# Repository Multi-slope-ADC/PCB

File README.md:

# High-resolution multislope ADC - MiDi

KiCad 10 project for the MiDi build of the multislope ADC developed from Kleinstein's design and Rerouter's PCB. The schematic documents the original circuit before the 2026 modifications, as saved on 18 October 2026.

## Project and downloads

Open [the KiCad project](High%20Resolution%20Multislope%20converter-modified%20rev%202.kicad_pro) with KiCad 10 and the standard KiCad symbol, footprint and 3D model libraries. Project-specific symbols are included and use relative library paths. Exports were generated with KiCad 10.0.7.

| File | Contents |
| --- | --- |
| [Schematic PDF](docs/Schematic.pdf) | Current schematic, white background and KiCad Classic colours |
| [Schematic PNG](https://raw.githubusercontent.com/Multi-slope-ADC/PCB/refs/heads/MiDi/docs/Schematic.png) | Full-page preview |
| [Complete schematic BOM](bom/BOM-all.csv) | 231 positions, including 15 marked DNP |
| [BOM excluding DNP](bom/BOM-fitted.csv) | 216 positions, following the saved schematic flags |
| [Interactive PCB viewer](https://htmlpreview.github.io/?https://github.com/Multi-slope-ADC/PCB/blob/MiDi/bom/ibom.html) | Board footprints, values and routing; [download HTML](bom/ibom.html) to open locally |
| [PCB PDF](docs/PCB.pdf) | Colour copper and paste layer plots with silkscreen and drawing frame |
| [Gerber and drill files](gerber_to_order/) | Direct exports of the preserved PCB; [ZIP](gerber_to_order/MiDi-Gerbers.zip) |

## Schematic

## PCB views

## Assembled board

## Background and credits

- Original design discussion: [DIY high-resolution multi-slope converter](https://www.eevblog.com/forum/metrology/diy-high-resolution-multi-slope-converter/).
- Related design discussion: [Multislope design](https://www.eevblog.com/forum/projects/multislope-design/).
- PCB ancestry: [Rerouter/Multislope-ADC-PCB](https://github.com/Rerouter/Multislope-ADC-PCB).
- Interactive PCB viewer generated with [InteractiveHtmlBom](https://github.com/openscopeproject/InteractiveHtmlBom).

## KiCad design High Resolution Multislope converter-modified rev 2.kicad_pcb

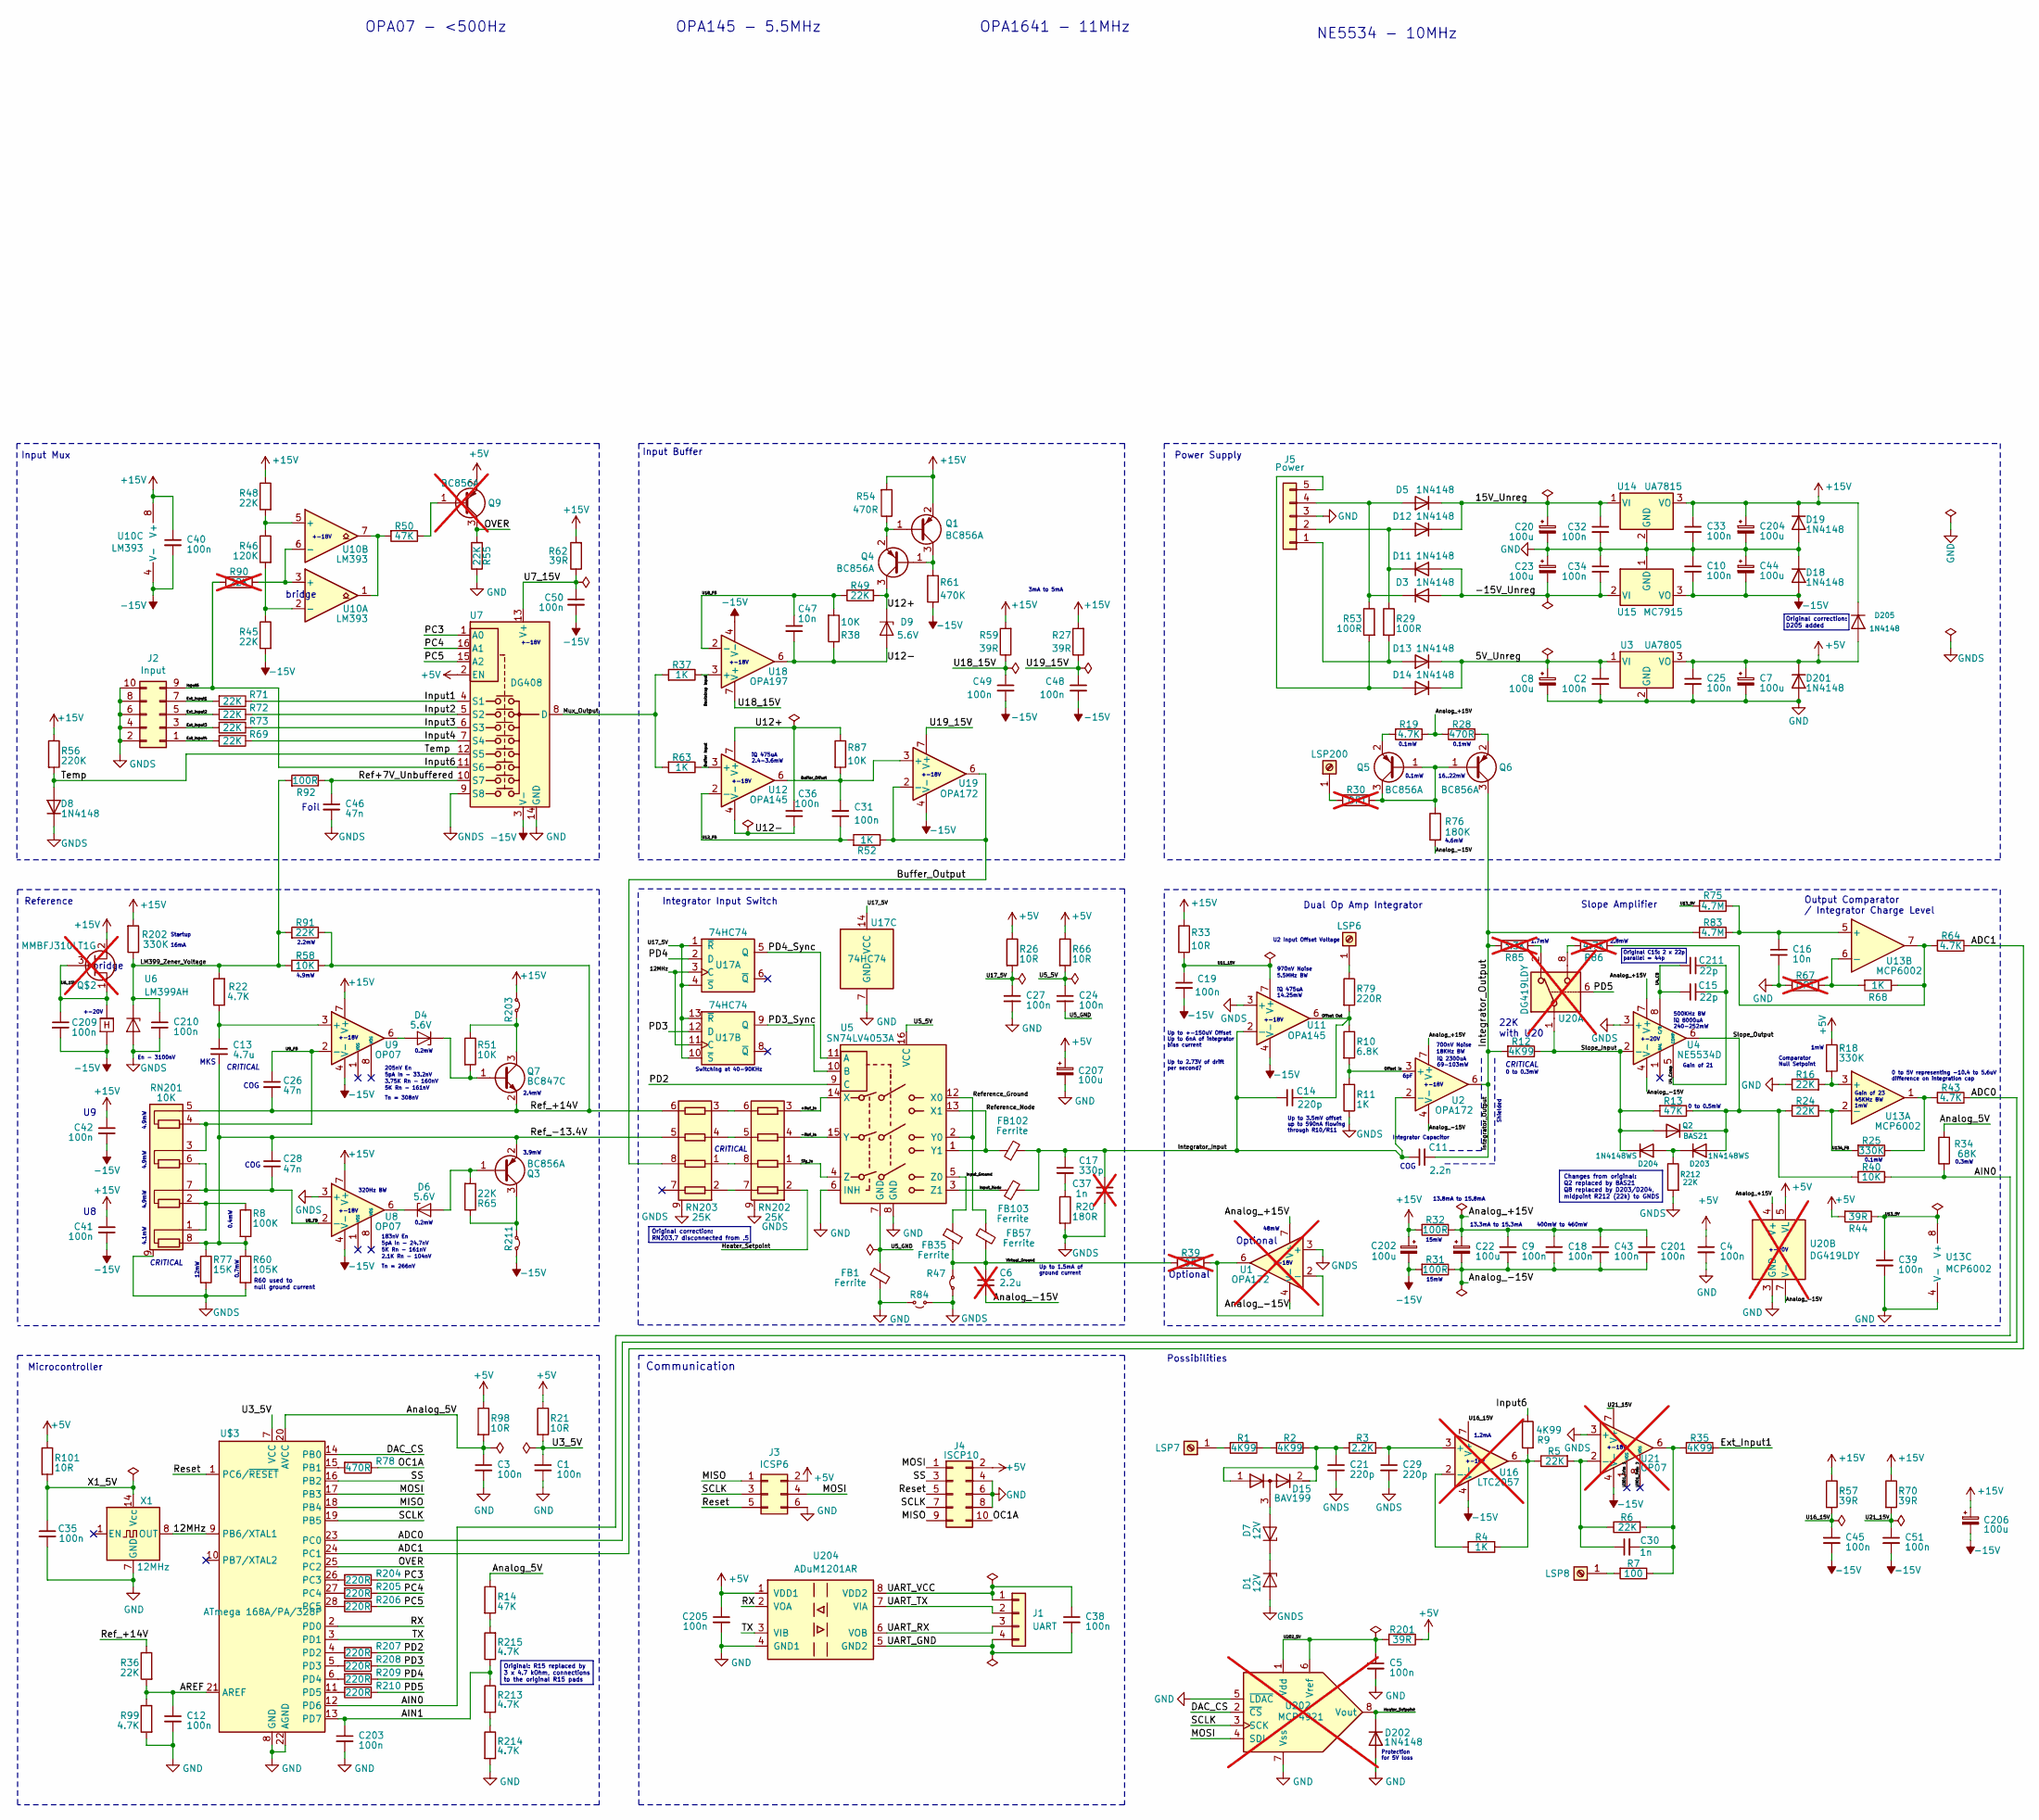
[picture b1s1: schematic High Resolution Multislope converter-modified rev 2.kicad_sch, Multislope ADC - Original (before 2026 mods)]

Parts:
C1, C2, C3, C4, C5, C9, C10, C12, C18, C19, C24, C25, C27, C32, C33, C34, C35, C36, C38, C39, C40, C41, C42, C43, C45, C48, C49, C50, C51, C201, C203, C205, C209, C210: 100n; C_0805_2012Metric; Manufacturer Part Number 08055C104KAT2A
C6: 2.2u; C_0805_2012Metric; Manufacturer Part Number CL21B225KAFNNNE; not fitted
C7, C8, C20, C22, C23, C44, C202, C204, C206, C207: 100u; CP_Radial_D8.0mm_P3.50mm; Manufacturer Part Number EEU-EB1J101
C11: 2.2n; C_0805_2012Metric; Manufacturer Part Number C2012C0G1H222J085AA
C13: 4.7u; C_Rect_L7.2mm_W7.2mm_P5.00mm_FKS2_FKP2_MKS2_MKP2; Manufacturer Part Number MKS2C044701M00KSSD
C14, C21, C29: 220p; C_0805_2012Metric; Manufacturer Part Number CL21C221JBANNNC
C15, C211: 22p; C_0805_2012Metric; Manufacturer Part Number CL21C220JBANNNC
C16, C47: 10n; C_0805_2012Metric; Manufacturer Part Number CGA4C2C0G1H103J060AA
C17: 330p; C_0805_2012Metric; Manufacturer Part Number C0805C331J5GACTU
C26, C28, C46: 47n; C_0805_2012Metric; Manufacturer Part Number C0805C473K3GECAUTO
C30: 1n; C_0805_2012Metric; Manufacturer Part Number 885012007063
C31: 100n; C_0805_2012Metric; Manufacturer Part Number C0805C473K3GECAUTO
C37: 1n; C_0805_2012Metric; Manufacturer Part Number 885012007063; not fitted
D1, D7: 12V; D_SOD-323; Manufacturer Part Number DDZ12CSF-7
D3, D5, D8, D11, D12, D13, D14, D18, D19, D201, D202: 1N4148; D_SOD-323; Manufacturer Part Number 1N4148WS
D4, D6, D9: 5.6V; D_SOD-323; Manufacturer Part Number MM3Z5V6ST1G
D15: BAV199; SOT-23; Manufacturer Part Number BAV199LT1G
D203, D204: 1N4148WS; Manufacturer Part Number 1N4148WS
D205: 1N4148; Manufacturer Part Number 1N4148
FB1, FB35, FB57, FB102, FB103: Ferrite; L_0805_2012Metric; Manufacturer Part Number MMZ2012Y152BT000
J1: UART; PinHeader_1x04_P2.54mm_Vertical
J2: Input; PinHeader_2x05_P2.54mm_Vertical
J3: ICSP6; PinHeader_2x03_P2.54mm_Vertical
J4: ISCP10; PinHeader_2x05_P2.54mm_Vertical
J5: Power; PinHeader_1x05_P2.54mm_Vertical
LSP6: INTX; PinHeader_1x01_P2.54mm_Vertical
LSP7: Input+; PinHeader_1x01_P2.54mm_Vertical
LSP8: Input-; PinHeader_1x01_P2.54mm_Vertical
LSP200: BIAS; PinHeader_1x01_P2.54mm_Vertical
Q1, Q3, Q4, Q5, Q6: BC856A; SOT-23; Manufacturer Part Number BC856A,215
Q2: BAS21; SOT-23; Manufacturer Part Number BAS21HMFHT116
Q7: BC847C; SOT-23; Manufacturer Part Number BC847CLT1G
Q9: BC856A; SOT-23; Manufacturer Part Number BC856A,215; not fitted
Q$2: MMBFJ310LT1G; SOT-23; Manufacturer Part Number MMBFJ310LT1G; not fitted
R1, R2, R9, R12, R35: 4K99; R_0805_2012Metric; Manufacturer Part Number RR1220P-4991-D-M
R3: 2.2K; R_0805_2012Metric; Manufacturer Part Number RR1220P-222-D
R4, R11, R37, R52, R63, R68: 1K; R_0805_2012Metric; Manufacturer Part Number RR1220P-102-D
R5, R6, R16, R24, R36, R45, R48, R49, R55, R65, R69, R71, R72, R73, R91: 22K; R_0805_2012Metric; Manufacturer Part Number RR1220P-223-D
R7: 100; R_0805_2012Metric; Manufacturer Part Number RR1220P-101-D
R8: 100K; R_0805_2012Metric; Manufacturer Part Number RR1220P-104-D
R10: 6.8K; R_0805_2012Metric; Manufacturer Part Number RR1220P-682-D
R13, R14, R50: 47K; R_0805_2012Metric; Manufacturer Part Number RR1220P-473-D
R18, R25, R202: 330K; R_0805_2012Metric; Manufacturer Part Number RR1220P-334-D
R19, R22, R43, R64, R99: 4.7K; R_0805_2012Metric; Manufacturer Part Number RR1220P-472-D
R20: 180R; R_0805_2012Metric; Manufacturer Part Number RR1220P-181-D
R21, R26, R33, R66, R98, R101: 10R; R_0805_2012Metric; Manufacturer Part Number RR1220Q-100-D
R27, R44, R57, R59, R62, R70, R201: 39R; R_0805_2012Metric; Manufacturer Part Number RR1220Q-390-D
R28, R54, R78: 470R; R_0805_2012Metric; Manufacturer Part Number RR1220P-471-D
R29, R31, R32, R53, R92: 100R; R_0805_2012Metric; Manufacturer Part Number RR1220P-101-D
R30, R67: OPT; R_0805_2012Metric; not fitted
R34: 68K; R_0805_2012Metric; Manufacturer Part Number RR1220P-683-D
R38, R40, R51, R58, R87: 10K; R_0805_2012Metric; Manufacturer Part Number RR1220P-103-D
R39: 0R; R_0805_2012Metric; not fitted
R46: 120K; R_0805_2012Metric; Manufacturer Part Number RR1220P-124-D
R47, R203, R211: Jumper (closed); SolderJumper-2_P1.3mm_Open_RoundedPad1.0x1.5mm
R56: 220K; R_0805_2012Metric; Manufacturer Part Number RR1220P-224-D
R60: 105K; R_0805_2012Metric; Manufacturer Part Number RR1220P-1053-D-M
R61: 470K; R_0805_2012Metric; Manufacturer Part Number RR1220P-474-D
R75, R83: 4.7M; R_0805_2012Metric; Manufacturer Part Number GWCR0805-4M7FT5
R76: 180K; R_0805_2012Metric; Manufacturer Part Number RR1220P-184-D
R77: 15K; R_0805_2012Metric; Manufacturer Part Number RR1220P-153-D
R79, R204, R205, R206, R207, R208, R209, R210: 220R; R_0805_2012Metric; Manufacturer Part Number RR1220P-221-D
R84: Jumper (open); SolderJumper-2_P1.3mm_Open_RoundedPad1.0x1.5mm
R85: 3.3K; R_0805_2012Metric; Manufacturer Part Number RR1220P-332-D; not fitted
R86: 4.7K; R_0805_2012Metric; Manufacturer Part Number RR1220P-472-D; not fitted
R90: 22K; R_0805_2012Metric; Manufacturer Part Number RR1220P-223-D; not fitted
R212: 22K
R213, R214, R215: 4.7K
RN201: 10K; MSOP-8_3x3mm_P0.65mm; Manufacturer Part Number MORNTA1002AT5
RN202, RN203: 25K; MSOP-8_3x3mm_P0.65mm; Manufacturer Part Number MORNTA2502AT5
U1: OPA172; SOIC-8_3.9x4.9mm_P1.27mm; Manufacturer Part Number OPA172IDR; not fitted
U2, U19: OPA172; SOIC-8_3.9x4.9mm_P1.27mm; Manufacturer Part Number OPA172IDR
U3: UA7805; TO-220-3_Vertical; Manufacturer Part Number UA7805CKCT
U4: NE5534D; SOIC-8_3.9x4.9mm_P1.27mm; Manufacturer Part Number NE5534DRE4
U5: SN74LV4053A; SOIC-16_3.9x9.9mm_P1.27mm; Manufacturer Part Number SN74LV4053ADR
U6: LM399AH; TO-46-4; Manufacturer Part Number LM399AH
U7: DG408; SOIC-16_3.9x9.9mm_P1.27mm; Manufacturer Part Number DG408DY-E3
U8, U9: OP07; SOIC-8_3.9x4.9mm_P1.27mm; Manufacturer Part Number OP07CDR
U10: LM393; SOIC-8_3.9x4.9mm_P1.27mm; Manufacturer Part Number LM393ADRG4
U11, U12: OPA145; SOIC-8_3.9x4.9mm_P1.27mm; Manufacturer Part Number OPA145IDR
U13: MCP6002; SOIC-8_3.9x4.9mm_P1.27mm; Manufacturer Part Number MCP6002T-I/SN
U14: UA7815; TO-220-3_Vertical; Manufacturer Part Number UA7815CKCT
U15: MC7915; TO-220-3_Vertical; Manufacturer Part Number MC7915ACTG
U16: LTC2057; SOIC-8_3.9x4.9mm_P1.27mm; Manufacturer Part Number LTC2057IS8#PBF; not fitted
U17: 74HC74; SOIC-14_3.9x8.7mm_P1.27mm; Manufacturer Part Number 74HC74D,653
U18: OPA197; SOIC-8_3.9x4.9mm_P1.27mm; Manufacturer Part Number OPA197IDR
U20: DG419LDY; SOIC-8_3.9x4.9mm_P1.27mm; Manufacturer Part Number DG419LDY+; not fitted
U21: OP07; SOIC-8_3.9x4.9mm_P1.27mm; Manufacturer Part Number OP07CDR; not fitted
U202: MCP4921; SOIC-8_3.9x4.9mm_P1.27mm; Manufacturer Part Number MCP4921-E/SN; not fitted
U204: ADuM1201AR; SOIC-8_3.9x4.9mm_P1.27mm; Manufacturer Part Number ADUM1201ARZ-RL7
U$3: ATmega 168A/PA/328P; DIP-28_W7.62mm_Socket_LongPads; Manufacturer Part Number ATmega48A/48PA/88A/88PA/168A/168PA/328/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
X1: 12MHz; Oscillator_DIP-14

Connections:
+5V: C4.1, C7.1, C25.1, C205.1, C207.1, D201.1 (K), D205.2 (A), J3.2, J4.2, Q9.2 (E), R18.1, R21.1, R26.1, R44.2, R66.1, R98.1, R101.1, R201.1, U3.3 (VO), U7.2 (EN), U20.5 (VL), U204.1 (VDD1); also elsewhere on the board
+15V: C33.1, C40.1, C41.1, C42.1, C202.1, C204.1, C206.1, D19.1 (K), D205.1 (K), Q1.2 (E), Q$2.2 (S), R27.2, R32.2, R33.1, R48.1, R54.2, R56.1, R57.1, R59.2, R62.2, R70.1, R202.2, R203.2 (B), U8.7 (V+), U9.7 (V+), U10.8 (V+), U14.3 (VO); also elsewhere on the board
-15V: C10.2, C19.2, C40.2, C41.2, C42.2, C44.2, C45.2, C48.2, C49.2, C50.2, C51.2, C202.2, C206.2, C209.2, D18.2 (A), R31.2, R45.2, R61.1, R211.2 (B), U6.4 (-), U7.3 (V-), U8.4 (V-), U9.4 (V-), U10.4 (V-), U11.4 (V-), U15.3 (VO), U16.4 (V-), U18.4 (V-), U19.4 (V-), U21.4 (V-); also elsewhere on the board
/5V_Unreg: C2.1, C8.1, D13.1 (K), D14.1 (K), U3.1 (VI)
/15V_Unreg: C20.1, C32.1, D5.1 (K), D12.1 (K), U14.1 (VI)
/16MHz: U17.3 (C), U17.11 (C), U$3.9 (PB6/XTAL1), X1.8 (OUT)
/+Ref_In: RN202.3 (R3.1), U5.14 (X); also elsewhere on the board
/-15V_Unreg: C23.2, C34.2, D3.2 (A), D11.2 (A), U15.2 (VI)
/-Ref_In: RN202.4 (R4.1), U5.15 (Y); also elsewhere on the board
/ADC0: R43.1, U$3.23 (PC0)
/ADC1: R64.1, U$3.24 (PC1)
/AIN0: R34.1, R40.1, U$3.12 (PD6)
/AIN1: C203.1, R213.1, R215.1, U$3.13 (PD7); also elsewhere on the board
/AREF: C12.1, R36.2, R99.1, U$3.21 (AREF)
/Analog_5V: C3.1, R14.1, R34.2, R98.2, U$3.20 (AVCC)
/Analog_+15V: C9.1, C18.1, C22.1, C43.1, C201.1, R19.1, R28.1, R32.1, U1.7 (V+), U2.7 (V+), U4.7 (V+), U20.4 (V+)
/Analog_-15V: C6.2, C9.2, C18.2, C22.2, C43.2, C201.2, R31.1, R76.2, U1.4 (V-), U2.4 (V-), U4.4 (V-), U20.7 (V-)
/Bootstrap Input: R37.1, U18.3 (+)
/Buffer Input: R63.1, U12.3 (+)
/Buffer_Offset: C31.2, R87.2, U12.6, U19.3 (+)
/Buffer_Output: R52.1, RN203.8 (R1.2), U19.2 (-), U19.6; also elsewhere on the board
/DAC_CS: U202.2 (~CS), U$3.14 (PB0)
/Ext_Input1: J2.7, R35.1, R71.2
/Ext_Input2: J2.5, R72.2
/Ext_Input3: J2.3, R73.2
/Ext_Input4: J2.1, R69.2
/Heater_Setpoint: D202.1 (K), RN202.2 (R2.1), U202.8 (Vout); also elsewhere on the board
/Input1: R71.1, U7.4 (S1)
/Input2: R72.1, U7.5 (S2)
/Input3: R73.1, U7.6 (S3)
/Input4: R69.1, U7.7 (S4)
/Input6: J2.9, R9.1, R90.2, U7.11 (S6)
/Input_Ground: FB35.1, U5.5 (Z0)
/Input_Node: FB103.1, U5.3 (Z1)
/Integrator_Input: C11.1, C14.1, C17.1, C37.1, FB102.2, FB103.2, U2.2 (-), U11.2 (-); also elsewhere on the board
/Integrator_Output: C11.2, Q6.3 (C), R12.2, R83.2, R85.2, U2.6; also elsewhere on the board
/LM399_Zener_Voltage: C210.1, R22.2, R58.2, R91.2, R92.2, R202.1, U6.1 (K); also elsewhere on the board
/MISO: J3.1, J4.9, U$3.18 (PB4)
/MOSI: J3.4, J4.1, U202.4 (SDI), U$3.17 (PB3)
/Mux_Output: R37.2, R63.2, U7.8 (D); also elsewhere on the board
/OC1A: J4.10, R78.1
/OVER: Q9.3 (C), R55.2, U$3.25 (PC2)
/Offset In: R10.2, R11.2, U2.3 (+)
/Offset Out: C14.2, R10.1, R79.2, U11.6
/PC3: R204.1, U7.1 (A0)
/PC4: R205.1, U7.16 (A1)
/PC5: R206.1, U7.15 (A2)
/PD2: R207.1, U5.9 (C)
/PD3: R208.1, U17.12 (D)
/PD3_Sync: U5.10 (B), U17.9 (Q)
/PD4: R209.1, U17.2 (D)
/PD4_Sync: U5.11 (A), U17.5 (Q)
/PD5: R210.1, U20.6
/RX: U204.2 (VOA), U$3.2 (PD0)
/Ref+7V_Unbuffered: C46.1, R92.1, U7.10 (S7)
/Ref_+14V: C26.2, Q7.2 (E), R36.1, R58.1, R91.1, RN201.5 (R4.2), RN203.6 (R3.2); also elsewhere on the board
/Ref_-13.4V: C13.2, C28.2, Q3.2 (E), R8.2, R60.1, R77.1, RN201.8 (R1.1), RN203.5 (R4.2), RN203.7 (R2.2); also elsewhere on the board
/Reference_Ground: FB57.1, U5.2 (Y0), U5.12 (X0)
/Reference_Node: FB102.1, U5.1 (Y1), U5.13 (X1)
/Reset: J3.5, J4.5, U$3.1 (PC6/~RESET)
/SCLK: J3.3, J4.7, U202.3 (SCK), U$3.19 (PB5)
/SS: J4.3, U$3.16 (PB2)
/Sig_In: RN202.1 (R1.1), U5.4 (Z); also elsewhere on the board
/Slope_Input: D204.1 (K), Q2.1 (A), Q2.2 (NC), R12.1, R13.2, U4.2 (-), U20.1; also elsewhere on the board
/Slope_Output: D203.2 (A), Q2.3 (K), R13.1, R24.2, R40.2, U4.6; also elsewhere on the board
/TX: U204.3 (VIB), U$3.3 (PD1)
/Temp: D8.2 (A), R56.2, U7.12 (S5)
/U4_Bal: U4.1 (BAL)
/U4_CB: C15.1, C211.1, U4.8 (C/B)
/U4_Comp: C15.2, C211.2, U4.5 (COMP)
/U5_5V: C24.1, R66.2, U5.16 (VCC)
/U5_GND: C24.2, FB1.1, U5.7 (GND)
/U6_15V: C209.1, Q$2.1 (D), Q$2.3 (G), U6.3 (+)
/U7_15V: C50.1, R62.1, U7.13 (V+)
/U8_FB: C28.1, RN201.6 (R3.1), RN201.7 (R2.2), U8.2 (-); also elsewhere on the board
/U8_Trim 1: U8.1 (VOS)
/U8_Trim 2: U8.8 (VOS)
/U9_FB: C26.1, RN201.3 (R3.2), RN201.4 (R4.1), U9.2 (-); also elsewhere on the board
/U9_Trim 1: U9.1 (VOS)
/U9_Trim 2: U9.8 (VOS)
/U11_15V: C19.1, R33.2, U11.7 (V+)
/U12+: C36.1, D9.1 (K), Q4.3 (C), R49.2, R87.1, U12.7 (V+)
/U12-: C36.2, C47.2, D9.2 (A), R38.1, U12.4 (V-), U18.6
/U12_FB: C31.1, R52.2, U12.2 (-)
/U13A_FB: R24.1, R25.2, U13.2 (-)
/U13_5V: C39.1, R44.1, R75.2, U13.8 (V+)
/U16_15V: C45.1, R57.2, U16.7 (V+)
/U17_5V: C27.1, R26.2, U17.1 (~R), U17.4 (~S), U17.10 (~S), U17.13 (~R), U17.14 (VCC)
/U18_15V: C49.1, R59.1, U18.7 (V+)
/U18_FB: C47.1, R38.2, R49.1, U18.2 (-)
/U19_15V: C48.1, R27.1, U19.7 (V+)
/U21_15V: C51.1, R70.2, U21.7 (V+)
/U202_5V: C5.1, R201.2, U202.1 (Vdd), U202.6 (Vref)
/U301_Trim 1: U21.1 (VOS)
/U301_Trim 2: U21.8 (VOS)
/U$3_5V: C1.1, R21.2, U$3.7 (VCC)
/UART_GND: C38.2, J1.4, U204.5 (GND2)
/UART_RX: J1.3, U204.6 (VOB)
/UART_TX: J1.2, U204.7 (VIA)
/UART_VCC: C38.1, J1.1, U204.8 (VDD2)
/Virtual_Ground: C6.1, FB35.2, FB57.2, R39.2, R47.1 (A)
/X1_5V: C35.1, R101.2, X1.14 (Vcc)
/X1_Enable: X1.1 (EN)
GND: C1.2, C2.2, C3.2, C4.2, C5.2, C7.2, C8.2, C10.1, C12.2, C16.2, C20.2, C23.1, C25.2, C27.2, C32.2, C33.2, C34.1, C35.2, C39.2, C44.1, C203.2, C204.2, C205.2, C207.2, D18.1 (K), D19.2 (A), D201.2 (A), D202.2 (A), FB1.2, J3.6, J4.4, J4.6, J4.8, J5.3, R16.1, R55.1, R67.2, R84.1 (A), R99.2, R214.2, U3.2 (GND), U5.6 (INH), U5.8 (GND), U7.14 (GND), U13.4 (V-), U14.2 (GND), U15.1 (GND), U17.7 (GND), U20.3 (GND), U202.5 (~LDAC), U202.7 (Vss), U204.4 (GND1), U$3.8 (GND), U$3.22 (AGND), X1.7 (GND); also elsewhere on the board
GNDS: C21.2, C29.2, C37.2, C46.2, C210.2, D1.2 (A), D8.1 (K), J2.2, J2.4, J2.6, J2.8, J2.10, R11.1, R20.2, R47.2 (B), R60.2, R77.2, R84.2 (B), R212.2, RN201.9 (Pad), RN202.9 (Pad), RN203.9 (Pad), U1.3 (+), U4.3 (+), U6.2 (A), U7.9 (S8), U8.3 (+), U11.3 (+), U21.3 (+); also elsewhere on the board
unnamed: C13.1, R22.1, U9.3 (+)
unnamed: C16.1, R75.1, R83.1, U13.5 (+)
unnamed: C17.2, R20.1
unnamed: C21.1, D15.1 (A), D15.2 (K), R2.1, R3.2
unnamed: C29.1, R3.1, U16.3 (+)
unnamed: C30.1, R5.2, R6.1, U21.2 (-)
unnamed: C30.2, R6.2, R7.1, R35.2, U21.6
unnamed: D1.1 (K), D7.1 (K)
unnamed: D3.1 (K), D5.2 (A), J5.4, R53.1
unnamed: D4.1 (K), Q7.1 (B), R51.2
unnamed: D4.2 (A), U9.6
unnamed: D6.1 (K), U8.6
unnamed: D6.2 (A), Q3.1 (B), R65.2
unnamed: D11.1 (K), D12.2 (A), J5.2, R29.1
unnamed: D13.2 (A), J5.1, R29.2
unnamed: D14.2 (A), J5.5, R53.2
unnamed: D7.2 (A), D15.3 (common)
unnamed: D203.1 (K), D204.2 (A), R212.1
unnamed: LSP6.1, R79.1
unnamed: LSP7.1, R1.2
unnamed: LSP8.1, R7.2
unnamed: LSP200.1, R30.2
unnamed: Q1.1 (B), Q4.2 (E), R54.1
unnamed: Q1.3 (C), Q4.1 (B), R61.2
unnamed: Q3.3 (C), R65.1, R211.1 (A)
unnamed: Q5.1 (B), Q5.3 (C), Q6.1 (B), R30.1, R76.1
unnamed: Q5.2 (E), R19.2
unnamed: Q6.2 (E), R28.2
unnamed: Q7.3 (C), R51.1, R203.1 (A)
unnamed: Q9.1 (B), R50.1
unnamed: R1.1, R2.2
unnamed: R4.1, R5.1, R9.2, U16.6
unnamed: R4.2, U16.2 (-)
unnamed 138: R8.1, RN201.1 (R1.2), RN201.2 (R2.1); also elsewhere on the board
unnamed 139: R14.2, R215.2; also elsewhere on the board
unnamed: R16.2, R18.2, U13.3 (+)
unnamed: R25.1, R43.2, U13.1
unnamed: R39.1, U1.2 (-), U1.6
unnamed: R45.1, R46.2, U10.2 (-)
unnamed: R46.1, R48.2, U10.5 (+)
unnamed: R50.2, U10.1, U10.7
unnamed: R64.2, R68.1, R86.1, U13.7
unnamed: R67.1, R68.2, U13.6 (-)
unnamed: R78.2, U$3.15 (PB1)
unnamed: R85.1, U20.2
unnamed: R86.2, U20.8
unnamed: R90.1, U10.3 (+), U10.6 (-)
unnamed: R204.2, U$3.26 (PC3)
unnamed: R205.2, U$3.27 (PC4)
unnamed: R206.2, U$3.28 (PC5)
unnamed: R207.2, U$3.4 (PD2)
unnamed: R208.2, U$3.5 (PD3)
unnamed: R209.2, U$3.6 (PD4)
unnamed: R210.2, U$3.11 (PD5)
unnamed: R213.2, R214.1
unnamed 160: RN202.5 (R4.2), RN203.4 (R4.1); also elsewhere on the board
unnamed 161: RN202.6 (R3.2), RN203.3 (R3.1); also elsewhere on the board
unnamed 162: RN202.7 (R2.2), RN203.2 (R2.1); also elsewhere on the board
unnamed 163: RN202.8 (R1.2), RN203.1 (R1.1); also elsewhere on the board

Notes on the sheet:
Tn = 266nV
+-18V
COG
700nV Noise
Power Supply
1mW
Up to +-150uV Offset Up to 6nA of integrator bias current
0 to 0.3mW
2.4mW
CRITICAL
18KHz BW
Microcontroller
Up to 2.73V of drift per second?
183nV En
Gain of 23
Startup
970nV Noise
Shielded
bridge
0.1mW
+-20V
205nV En
15mW
5pA In - 33.2nV
Slope Amplifier
Input Mux
48mW
22K with U20
0.3mW
5K Rn - 161nV
3.75K Rn - 160nV
Possibilities
OPA07 - <500Hz
4.9mW
iQ 2300uA 69-103mW
Reference
5pA In - 24.7nV
Up to 3.5mV offset up to 590nA flowing through R10/R11
Optional
Input Buffer
